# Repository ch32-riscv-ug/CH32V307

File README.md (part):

# CH32V307

<!-- This file is generated from ch32-riscv-ug/ch32-device-data (index/ + evidence/ + pipeline/build/build_readme.py). Edit there, not here. -->

[Choose a part](#product-comparison) &middot; [Documents](#documents) &middot; [Pin maps](#pin-maps--alternate-functions) &middot; [Pin viewer](https://ch32-riscv-ug.github.io/ch32-device-data/pins.html?chip=CH32V303) &middot; [Errata](#errata) &middot; [Examples](#evt-examples) &middot; [Address map](#address-map)

## Quick start

Programming and debug: **2-wire SDI** (WCH-Link, `Serial Debug Interface`).

### Debug / serial defaults

Where these land **without writing a remap register**. SWD is live at reset; the UART pads are not -- the pin must still be put into alternate-function mode. See `route` in evidence/README.ja.md.

| Series | SWDIO | SWCLK | UART TX | UART RX |
|---|---|---|---|---|
| CH32V303 | PA13 | PA14 | PA9 (USART1); PA2 (USART2) | PA10 (USART1); PA3 (USART2) |
| CH32V305 | PA13 | PA14 | PA9 (USART1); PA2 (USART2) | PA10 (USART1); PA3 (USART2) |
| CH32V307 | PA13 | PA14 | PA9 (USART1); PA2 (USART2) | PA10 (USART1); PA3 (USART2) |
| CH32V317 | PA13 | PA14 | PA9 (USART1); PA2 (USART2) | PA10 (USART1); PA3 (USART2) |

### Datasheets and reference manual

- CH32V20x_30xDS0.PDF (datasheet): [English](https://ch32-riscv-ug.github.io/CH32V307/datasheet_en/CH32V20x_30xDS0.PDF) · [中文](https://ch32-riscv-ug.github.io/CH32V307/datasheet_zh/CH32V20x_30xDS0.PDF)
- CH32FV2x_V3xRM.PDF (reference manual): [English](https://ch32-riscv-ug.github.io/CH32V307/datasheet_en/CH32FV2x_V3xRM.PDF) · [中文](https://ch32-riscv-ug.github.io/CH32V307/datasheet_zh/CH32FV2x_V3xRM.PDF)

## Series

Flash and SRAM list every value the series has; more than one means it varies by part number, and the per-part values are in the comparison table below.

| Series | Core | ISA | Flash | SRAM | Main clock | VDD | Packages | Products | Official |
|---|---|---|---|---|---|---|---|---|---|
| **CH32V303** | QingKe V4F | RV32IMACF | 128K/256K | 32K/64K | 144 MHz | 2.4-3.6V | LQFP100,LQFP48,LQFP64M | 5 | [en](https://www.wch-ic.com/products/CH32V303.html) / [zh](https://www.wch.cn/products/CH32V303.html) |
| **CH32V305** | QingKe V4F | RV32IMACF | 128K/256K | 32K/64K | 144 MHz | 2.4-3.6V | LQFP48,LQFP64M,QFN28,TSSOP20 | 4 | [en](https://www.wch-ic.com/products/CH32V305.html) / [zh](https://www.wch.cn/products/CH32V305.html) |
| **CH32V307** | QingKe V4F | RV32IMACF | 256K | 64K | 144 MHz | 2.4-3.6V | LQFP100,LQFP64M,QFN68 | 3 | [en](https://www.wch-ic.com/products/CH32V307.html) / [zh](https://www.wch.cn/products/CH32V307.html) |
| **CH32V317** | QingKe V4F | RV32IMACF | 256K | 64K | 144 MHz | 2.4-3.6V | LQFP100,QFN68 | 2 | [en](https://www.wch-ic.com/products/CH32V317.html) / [zh](https://www.wch.cn/products/CH32V317.html) |

## Product comparison

### CH32V303 product comparison

Only the 14 rows that differ between these 5 products; the other 11 are the same for all of them.

| | [CH32V303&#8203;CBT6](https://ch32-riscv-ug.github.io/ch32-device-data/pins.html?chip=CH32V303CBT6)&#8203;(LQFP48) | [CH32V303&#8203;RBT6](https://ch32-riscv-ug.github.io/ch32-device-data/pins.html?chip=CH32V303RBT6)&#8203;(LQFP64M) | [CH32V303&#8203;RCT6](https://ch32-riscv-ug.github.io/ch32-device-data/pins.html?chip=CH32V303RCT6)&#8203;(LQFP64M) | [CH32V303&#8203;RCT7](https://ch32-riscv-ug.github.io/ch32-device-data/pins.html?chip=CH32V303RCT7)&#8203;(LQFP64M) | [CH32V303&#8203;VCT6](https://ch32-riscv-ug.github.io/ch32-device-data/pins.html?chip=CH32V303VCT6)&#8203;(LQFP100) |
|---|---|---|---|---|---|
| **Flash (zero-wait)** | 128K | 128K | 256K | 256K | 256K |
| **SRAM** | 32K | 32K | 64K | 64K | 64K |
| **GPIO** | 37 | 51 | 51 | 51 | 80 |
| **Temperature** | -40..85C | -40..85C | -40..85C | -40..105C | -40..85C |
| Advanced-control (16-bit) | 1 | 1 | 4 | 4 | 4 |
| General-purpose (16-bit) | 3 | 3 | 4 | 4 | 4 |
| Basic (16-bit) | - | - | 2 | 2 | 2 |
| ADC/TKey Channel | 10 | 16 | 16 | 16 | 16 |
| USART/UART | 3 | 3 | 8 | 8 | 8 |
| SPI | 2 | 2 | 3 | 3 | 3 |
| RNG | - | - | 1 | 1 | 1 |
| I2S | - | - | 2 | 2 | 2 |
| SDIO | - | - | 1 | 1 | 1 |
| FSMC | - | - | - | - | 1 |

<details><summary>All 25 rows</summary>

| | [CH32V303&#8203;CBT6](https://ch32-riscv-ug.github.io/ch32-device-data/pins.html?chip=CH32V303CBT6)&#8203;(LQFP48) | [CH32V303&#8203;RBT6](https://ch32-riscv-ug.github.io/ch32-device-data/pins.html?chip=CH32V303RBT6)&#8203;(LQFP64M) | [CH32V303&#8203;RCT6](https://ch32-riscv-ug.github.io/ch32-device-data/pins.html?chip=CH32V303RCT6)&#8203;(LQFP64M) | [CH32V303&#8203;RCT7](https://ch32-riscv-ug.github.io/ch32-device-data/pins.html?chip=CH32V303RCT7)&#8203;(LQFP64M) | [CH32V303&#8203;VCT6](https://ch32-riscv-ug.github.io/ch32-device-data/pins.html?chip=CH32V303VCT6)&#8203;(LQFP100) |
|---|---|---|---|---|---|
| **Flash (zero-wait)** | 128K | 128K | 256K | 256K | 256K |
| **SRAM** | 32K | 32K | 64K | 64K | 64K |
| **GPIO** | 37 | 51 | 51 | 51 | 80 |
| **Temperature** | -40..85C | -40..85C | -40..85C | -40..105C | -40..85C |
| Code FLASH, total (bytes) | 480K | 480K | 480K | 480K | 480K |
| Advanced-control (16-bit) | 1 | 1 | 4 | 4 | 4 |
| General-purpose (16-bit) | 3 | 3 | 4 | 4 | 4 |
| Timer Watchdog | 2 (WWDG + IWDG) | 2 (WWDG + IWDG) | 2 (WWDG + IWDG) | 2 (WWDG + IWDG) | 2 (WWDG + IWDG) |
| Basic (16-bit) | - | - | 2 | 2 | 2 |
| SysTick (64-bit) | Supported | Supported | Supported | Supported | Supported |
| RTC | Supported | Supported | Supported | Supported | Supported |
| ADC/TKey Unit | 2 | 2 | 2 | 2 | 2 |
| ADC/TKey Channel | 10 | 16 | 16 | 16 | 16 |
| DAC (Unit) | 2 | 2 | 2 | 2 | 2 |
| OPA/CMP | 4 | 4 | 4 | 4 | 4 |
| USART/UART | 3 | 3 | 8 | 8 | 8 |
| SPI | 2 | 2 | 3 | 3 | 3 |
| RNG | - | - | 1 | 1 | 1 |
| I2C | 2 | 2 | 2 | 2 | 2 |
| CAN | 1 | 1 | 1 | 1 | 1 |
| USBHD | 1 | 1 | 1 | 1 | 1 |
| I2S | - | - | 2 | 2 | 2 |
| CPU main frequency | Max: 144MHz | Max: 144MHz | Max: 144MHz | Max: 144MHz | Max: 144MHz |
| SDIO | - | - | 1 | 1 | 1 |
| FSMC | - | - | - | - | 1 |

</details>

### CH32V305 product comparison

Only the 13 rows that differ between these 4 products; the other 12 are the same for all of them.

| | [CH32V305&#8203;CCT6](https://ch32-riscv-ug.github.io/ch32-device-data/pins.html?chip=CH32V305CCT6)&#8203;(LQFP48) | [CH32V305&#8203;FBP6](https://ch32-riscv-ug.github.io/ch32-device-data/pins.html?chip=CH32V305FBP6)&#8203;(TSSOP20) | [CH32V305&#8203;GBU6](https://ch32-riscv-ug.github.io/ch32-device-data/pins.html?chip=CH32V305GBU6)&#8203;(QFN28) | [CH32V305&#8203;RBT6](https://ch32-riscv-ug.github.io/ch32-device-data/pins.html?chip=CH32V305RBT6)&#8203;(LQFP64M) |
|---|---|---|---|---|
| **Flash (zero-wait)** | 256K | 128K | 128K | 128K |
| **SRAM** | 64K | 32K | 32K | 32K |
| **GPIO** | 41 | 17 | 24 | 51 |
| Code FLASH, total (bytes) | 480K | 224K | 224K | 480K |
| ADC/TKey Channel | 16 | 1 | 6 | 16 |
| DAC (Unit) | 2 | DAC2 | 2 | 2 |
| OPA/CMP | 4 | - | OPA3 | 4 |
| USART/UART | 5 | USART1 USART3 | USART1 USART3 UART4 UART5 UART7 | 5 |
| SPI | 3 | SPI2 | 3 | 3 |
| I2S | 2 | I2S2 | 2 | 2 |
| CAN | 2 | CAN2 | CAN2 | 2 |
| USBHD | 1 | - | - | 1 |
| SDIO | - | - | 1 | 1 |

<details><summary>All 25 rows</summary>

| | [CH32V305&#8203;CCT6](https://ch32-riscv-ug.github.io/ch32-device-data/pins.html?chip=CH32V305CCT6)&#8203;(LQFP48) | [CH32V305&#8203;FBP6](https://ch32-riscv-ug.github.io/ch32-device-data/pins.html?chip=CH32V305FBP6)&#8203;(TSSOP20) | [CH32V305&#8203;GBU6](https://ch32-riscv-ug.github.io/ch32-device-data/pins.html?chip=CH32V305GBU6)&#8203;(QFN28) | [CH32V305&#8203;RBT6](https://ch32-riscv-ug.github.io/ch32-device-data/pins.html?chip=CH32V305RBT6)&#8203;(LQFP64M) |
|---|---|---|---|---|
| **Flash (zero-wait)** | 256K | 128K | 128K | 128K |
| **SRAM** | 64K | 32K | 32K | 32K |
| **GPIO** | 41 | 17 | 24 | 51 |
| **Temperature** | -40..85C | -40..85C | -40..85C | -40..85C |
| Code FLASH, total (bytes) | 480K | 224K | 224K | 480K |
| Advanced-control (16-bit) | 4 | 4 | 4 | 4 |
| General-purpose (16-bit) | 4 | 4 | 4 | 4 |
| Basic (16-bit) | 2 | 2 | 2 | 2 |
| Timer Watchdog | 2 (WWDG + IWDG) | 2 (WWDG + IWDG) | 2 (WWDG + IWDG) | 2 (WWDG + IWDG) |
| SysTick (64-bit) | Supported | Supported | Supported | Supported |
| RTC | Supported | Supported | Supported | Supported |
| ADC/TKey Unit | 2 | 2 | 2 | 2 |
| ADC/TKey Channel | 16 | 1 | 6 | 16 |
| DAC (Unit) | 2 | DAC2 | 2 | 2 |
| OPA/CMP | 4 | - | OPA3 | 4 |
| RNG | 1 | 1 | 1 | 1 |
| USART/UART | 5 | USART1 USART3 | USART1 USART3 UART4 UART5 UART7 | 5 |
| SPI | 3 | SPI2 | 3 | 3 |
| I2S | 2 | I2S2 | 2 | 2 |
| I2C | 2 | 2 | 2 | 2 |
| CAN | 2 | CAN2 | CAN2 | 2 |
| USBHS (include PHY) | 1 | 1 | 1 | 1 |
| USBHD | 1 | - | - | 1 |
| CPU main frequency | Max: 144MHz | Max: 144MHz | Max: 144MHz | Max: 144MHz |
| SDIO | - | - | 1 | 1 |

</details>

### CH32V307 product comparison

Only the 3 rows that differ between these 3 products; the other 25 are the same for all of them.

| | [CH32V307&#8203;RCT6](https://ch32-riscv-ug.github.io/ch32-device-data/pins.html?chip=CH32V307RCT6)&#8203;(LQFP64M) | [CH32V307&#8203;VCT6](https://ch32-riscv-ug.github.io/ch32-device-data/pins.html?chip=CH32V307VCT6)&#8203;(LQFP100) | [CH32V307&#8203;WCU6](https://ch32-riscv-ug.github.io/ch32-device-data/pins.html?chip=CH32V307WCU6)&#8203;(QFN68) |
|---|---|---|---|
| **GPIO** | 51 | 80 | 54 |
| DVP | - | 1 | - |
| FSMC | - | 1 | - |

<details><summary>All 28 rows</summary>

| | [CH32V307&#8203;RCT6](https://ch32-riscv-ug.github.io/ch32-device-data/pins.html?chip=CH32V307RCT6)&#8203;(LQFP64M) | [CH32V307&#8203;VCT6](https://ch32-riscv-ug.github.io/ch32-device-data/pins.html?chip=CH32V307VCT6)&#8203;(LQFP100) | [CH32V307&#8203;WCU6](https://ch32-riscv-ug.github.io/ch32-device-data/pins.html?chip=CH32V307WCU6)&#8203;(QFN68) |
|---|---|---|---|
| **Flash (zero-wait)** | 256K | 256K | 256K |
| **SRAM** | 64K | 64K | 64K |
| **GPIO** | 51 | 80 | 54 |
| **Temperature** | -40..85C | -40..85C | -40..85C |
| Code FLASH, total (bytes) | 480K | 480K | 480K |
| Advanced-control (16-bit) | 4 | 4 | 4 |
| General-purpose (16-bit) | 4 | 4 | 4 |
| Basic (16-bit) | 2 | 2 | 2 |
| Timer Watchdog | 2 (WWDG + IWDG) | 2 (WWDG + IWDG) | 2 (WWDG + IWDG) |
| SysTick (64-bit) | Supported | Supported | Supported |
| RTC | Supported | Supported | Supported |
| ADC/TKey Unit | 2 | 2 | 2 |
| ADC/TKey Channel | 16 | 16 | 16 |
| DAC (Unit) | 2 | 2 | 2 |
| OPA/CMP | 4 | 4 | 4 |
| RNG | 1 | 1 | 1 |
| USART/UART | 8 | 8 | 8 |
| SPI | 3 | 3 | 3 |
| I2S | 2 | 2 | 2 |
| I2C | 2 | 2 | 2 |
| CAN | 2 | 2 | 2 |
| SDIO | 1 | 1 | 1 |
| USBHD | 1 | 1 | 1 |
| USBHS (include PHY) | 1 | 1 | 1 |
| Ethernet | 1G MAC+10M PHY | 1G MAC+10M PHY | 1G MAC+10M PHY |
| CPU main frequency | Max: 144MHz | Max: 144MHz | Max: 144MHz |
| DVP | - | 1 | - |
| FSMC | - | 1 | - |

</details>

### CH32V317 product comparison

Only the 2 rows that differ between these 2 products; the other 25 are the same for all of them.

| | [CH32V317&#8203;VCT6](https://ch32-riscv-ug.github.io/ch32-device-data/pins.html?chip=CH32V317VCT6)&#8203;(LQFP100) | [CH32V317&#8203;WCU6](https://ch32-riscv-ug.github.io/ch32-device-data/pins.html?chip=CH32V317WCU6)&#8203;(QFN68) |
|---|---|---|
| **GPIO** | 70 | 48 |
| DVP | 1 | - |

<details><summary>All 27 rows</summary>

| | [CH32V317&#8203;VCT6](https://ch32-riscv-ug.github.io/ch32-device-data/pins.html?chip=CH32V317VCT6)&#8203;(LQFP100) | [CH32V317&#8203;WCU6](https://ch32-riscv-ug.github.io/ch32-device-data/pins.html?chip=CH32V317WCU6)&#8203;(QFN68) |
|---|---|---|
| **Flash (zero-wait)** | 256K | 256K |
| **SRAM** | 64K | 64K |
| **GPIO** | 70 | 48 |
| **Temperature** | -40..85C | -40..85C |
| Code FLASH, total (bytes) | 480K | 480K |
| Advanced-control (16-bit)(2) | 4 | 4 |
| General-purpose (16-bit)(2) | 4 | 4 |
| Basic (16-bit) | 2 | 2 |
| Timer Watchdog | 2 (WWDG + IWDG) | 2 (WWDG + IWDG) |
| SysTick (64-bit) | Supported | Supported |
| RTC | Supported | Supported |
| ADC/TKey Unit | 2 | 2 |
| ADC/TKey Channel | 16 | 16 |
| DAC (Unit) | 2 | 2 |
| OPA | 4 | 4 |
| RNG | 1 | 1 |
| USART/UART | 8 | 8 |
| SPI | 3 | 3 |
| I2S | 2 | 2 |
| I2C | 2 | 2 |
| CAN | 2 | 2 |
| SDIO | 1 | 1 |
| USBHD | 1 | 1 |
| USBHS (include PHY) | 1 | 1 |
| Ethernet | MAC+10M/100M PHY | MAC+10M/100M PHY |
| DVP | 1 | - |
| CPU main frequency | Max: 144MHz | Max: 144MHz |

</details>

## Block diagrams

### CH32V303

System block diagram from the [WCH product page](https://www.wch-ic.com/products/CH32V303.html).

<details><summary>Internal block diagram (datasheet)</summary>

</details>

### CH32V305

<details><summary>Internal block diagram (datasheet)</summary>

</details>

### CH32V307

System block diagram from the [WCH product page](https://www.wch-ic.com/products/CH32V307.html).

<details><summary>Internal block diagram (datasheet)</summary>

</details>

### CH32V317

System block diagram from the [WCH product page](https://www.wch-ic.com/products/CH32V317.html).

<details><summary>Internal block diagram (datasheet)</summary>

</details>

## Documents

| Document | Kind | English | 中文 |
|---|---|---|---|
| CH32V20x_30xDS0.PDF | datasheet | [page](https://www.wch-ic.com/downloads/CH32V20x_30xDS0_PDF.html) [mirror](https://ch32-riscv-ug.github.io/CH32V307/datasheet_en/CH32V20x_30xDS0.PDF) v3.5 | [page](https://www.wch.cn/downloads/CH32V20x_30xDS0_PDF.html) [mirror](https://ch32-riscv-ug.github.io/CH32V307/datasheet_zh/CH32V20x_30xDS0.PDF) v3.5 |
| CH32FV2x_V3xRM.PDF | reference-manual | [page](https://www.wch-ic.com/downloads/CH32FV2x_V3xRM_PDF.html) [mirror](https://ch32-riscv-ug.github.io/CH32V307/datasheet_en/CH32FV2x_V3xRM.PDF) v2.5 | [page](https://www.wch.cn/downloads/CH32FV2x_V3xRM_PDF.html) [mirror](https://ch32-riscv-ug.github.io/CH32V307/datasheet_zh/CH32FV2x_V3xRM.PDF) v2.5 |
| CH32V307EVT.ZIP | evt | - | [page](https://www.wch.cn/downloads/CH32V307EVT_ZIP.html) [mirror](https://github.com/ch32-riscv-ug/CH32V307/tree/main/EVT) v3.2 |

### Evaluation boards

- board-manual:en: [CH32V30x Evaluation Board Reference-EN.pdf](https://ch32-riscv-ug.github.io/CH32V307/EVT/PUB/CH32V30x%20Evaluation%20Board%20Reference-EN.pdf)
- board-manual:zh: [CH32V30x评估板说明书.pdf](https://ch32-riscv-ug.github.io/CH32V307/EVT/PUB/CH32V30x%E8%AF%84%E4%BC%B0%E6%9D%BF%E8%AF%B4%E6%98%8E%E4%B9%A6.pdf)
- schematic-pdf: [CH32V30xSCH.pdf](https://ch32-riscv-ug.github.io/CH32V307/EVT/PUB/CH32V30xSCH.pdf)

13 board schematics under `EVT/PUB/SCHPCB/`: `CH32V303CBT6-R0`, `CH32V303RBT6-R1`, `CH32V303RCT6-R1`, `CH32V303VCT6-R0`, `CH32V303VCT6-R1`, `CH32V305FBP6-R0`, `CH32V305GBU6-R0`, `CH32V305RBT6-R1`, `CH32V307RCT6-R1`, `CH32V307VCT6-R0`, `CH32V307VCT6-R1`, `CH32V307WCU6-R0`, `CH32V317WCU6-R0`

## Packages & pinout drawings

Pinout drawings are in the datasheet (chapter *Pinouts*); each link opens at the page that carries the drawing:

| Package | Products | Datasheet | Outline |
|---|---|---|---|
| LQFP48 | CH32V303CBT6 | [en](https://ch32-riscv-ug.github.io/CH32V307/datasheet_en/CH32V20x_30xDS0.PDF#page=27) / [zh](https://ch32-riscv-ug.github.io/CH32V307/datasheet_zh/CH32V20x_30xDS0.PDF#page=22) | [drawing](https://raw.githubusercontent.com/ch32-riscv-ug/WCH-common/main/image/package_LQFP48.png) |
| LQFP64M | CH32V303RBT6, CH32V303RCT6, CH32V303RCT7, CH32V305RBT6, CH32V307RCT6 | [en](https://ch32-riscv-ug.github.io/CH32V307/datasheet_en/CH32V20x_30xDS0.PDF#page=27) / [zh](https://ch32-riscv-ug.github.io/CH32V307/datasheet_zh/CH32V20x_30xDS0.PDF#page=22) | [drawing](https://raw.githubusercontent.com/ch32-riscv-ug/WCH-common/main/image/package_LQFP64M.png) |
| LQFP100 | CH32V303VCT6, CH32V307VCT6 | [en](https://ch32-riscv-ug.github.io/CH32V307/datasheet_en/CH32V20x_30xDS0.PDF#page=27) / [zh](https://ch32-riscv-ug.github.io/CH32V307/datasheet_zh/CH32V20x_30xDS0.PDF#page=22) | [drawing](https://raw.githubusercontent.com/ch32-riscv-ug/WCH-common/main/image/package_LQFP100.png) |
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
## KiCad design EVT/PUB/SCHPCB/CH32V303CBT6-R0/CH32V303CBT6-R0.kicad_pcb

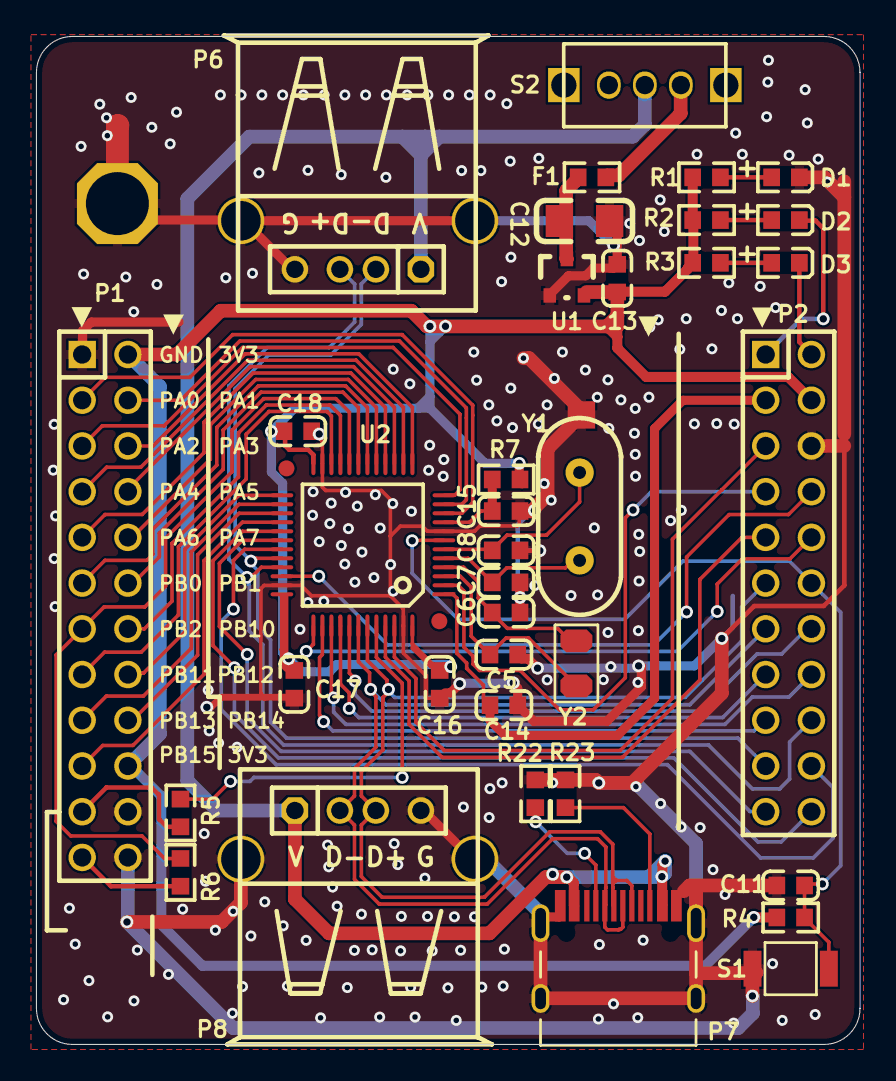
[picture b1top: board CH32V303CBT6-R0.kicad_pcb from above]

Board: 2 copper layers, 45.8 x 56.0 mm, 36 parts (0 on the bottom side), 55 nets.

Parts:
C5, C6: 12pF; 0603_C
C7, C8: 22pF; 0603_C
C11, C14, C15, C16, C17, C18: 0.1uF; 0603_C
C12: 10uF; 3216_C
C13: 2.2uF; 0603_C
D1: POWER red; 0603+
D2: LED1; 0603+
D3: LED2; 0603+
F1: 500mA; 0603
P1: HEADER 12x2; IDC24-2.54MM
P2: HEADER 11x2; IDC22-2.54MM
P6, P8: USB_A; USBAF
P7: TYPE-C; TYPE-C-Receptacle-2.0
R1, R2, R3: 1K; 0603
R4, R5, R6: 10K; 0603
R7: 0Ω; 0603
R22, R23: NC(5.1K); 0603
S1: KEY; 贴片按键
S2: SW; KEY2
U1: 6219P33M; SOT-23
U2: CH32V203CxT; LQFP48
Y1: 8M; XT_AT49
Y2: 32.768k; FC-135

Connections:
+5V: P6.1, P7.A4, P7.B4, P8.1, S2.1
BOOT0: R5.1, U2.44
BOOT1: P1.13, R6.1, U2.20
GND: C5.2, C6.2, C7.1, C8.1, C11.1, C12.2, C13.2, C14.2, C15.2, C16.1, C17.1, C18.1, D1.2, P1.1, P1.22, P1.24, P2.6, P6.0, P6.4, P7.0, P7.A1, P7.B1, P8.0, P8.4, R22.2, R23.2, S1.2, U1.1, U2.8, U2.23, U2.35, U2.47, Y1.0
LED1: D2.2, P2.1
LED2: D3.2, P2.2
NRST: C11.2, P2.12, R4.1, S1.1, U2.7
NetD1_1: D1.1, R1.1
NetD2_1: D2.1, R2.2
NetD3_1: D3.1, R3.2
NetF1_1: F1.1, S2.3
NetP1_21: P1.21, R5.2
NetP1_23: P1.23, R6.2
NetP7_A5: P7.A5, R22.1
NetP7_B5: P7.B5, R23.1
PA0: P1.3, U2.10
PA1: P1.4, U2.11
PA2: P1.5, U2.12
PA3: P1.6, U2.13
PA4: P1.7, U2.14
PA5: P1.8, U2.15
PA6: P1.9, U2.16
PA7: P1.10, U2.17
PA8: P2.22, U2.29
PA9: P2.21, U2.30
PA10: P2.20, U2.31
PA11: P2.19, P6.2, U2.32
PA12: P2.18, P6.3, U2.33
PA13: P2.8, U2.34
PA14: P2.10, U2.37
PA15: P2.17, U2.38
PB0: P1.11, U2.18
PB1: P1.12, U2.19
PB3: P2.16, U2.39
PB4: P2.15, U2.40
PB5: P2.14, U2.41
PB6: P2.13, P7.A7, P7.B7, P8.2, U2.42
PB7: P2.11, P7.A6, P7.B6, P8.3, U2.43
PB8: P2.9, U2.45
PB9: P2.5, U2.46
PB10: P1.14, U2.21
PB11: P1.15, U2.22
PB12: P1.16, U2.25
PB13: P1.17, U2.26
PB14: P1.18, U2.27
PB15: P1.19, U2.28
PC13: P2.7, U2.2
PC14: C5.1, U2.3, Y2.1
PC15: C6.1, U2.4, Y2.2
PD0: C7.2, U2.5, Y1.2
PD1: C8.2, U2.6, Y1.1
V5V: C12.1, F1.2, U1.3
VBAT: C14.1, P2.3, U2.1
VCC: C13.1, C16.2, C17.2, C18.2, P1.2, P1.20, P2.4, R1.2, R2.1, R3.1, R4.2, R7.1, U1.2, U2.24, U2.36, U2.48
VDDA: C15.1, R7.2, U2.9

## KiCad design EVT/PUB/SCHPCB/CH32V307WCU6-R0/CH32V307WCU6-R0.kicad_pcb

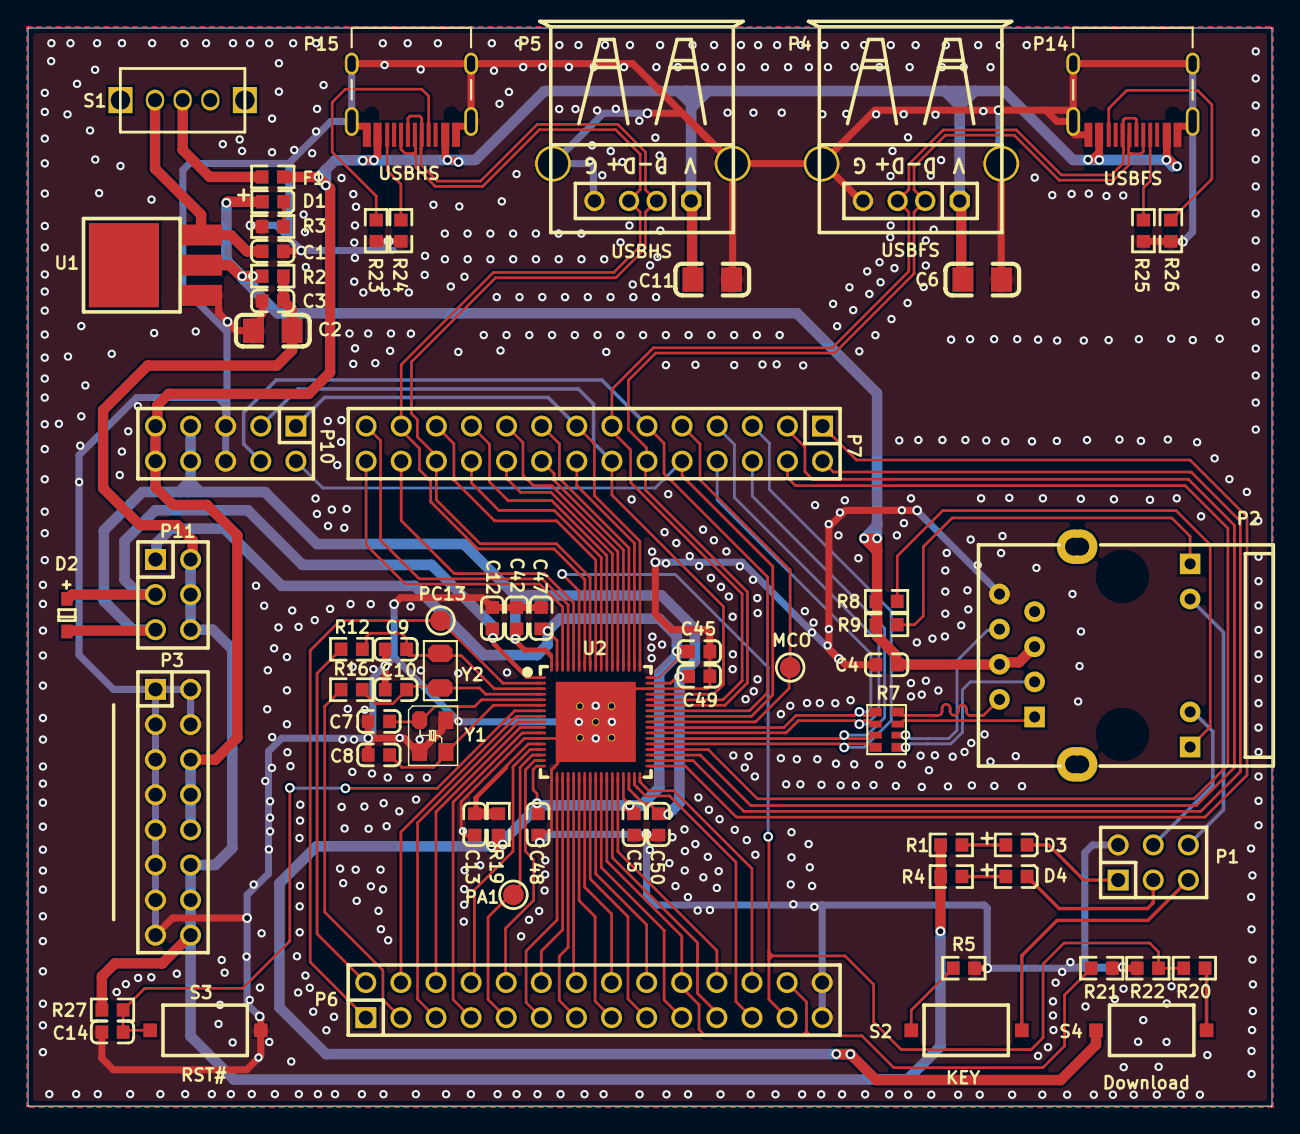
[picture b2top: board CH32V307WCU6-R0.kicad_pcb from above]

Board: 2 copper layers, 90.0 x 78.0 mm, 66 parts (0 on the bottom side), 88 nets.

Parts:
C1, C3, C4, C5, C12, C13, C14, C42, C45, C47, C48, C49, C50: 0.1uF; 0603_C
C2, C6, C11: 10uF; 3216_C
C7, C8: 22pF; 0603_C
C9, C10: 12pF; 0603_C
D1, D4: RED; 0603+
D2: B0520WS; SOD-323
D3: BLUE; 0603+
F1: 500mA; 0603
MCO: Testpoint; TESTPOINT1
P1: IO; IDC6-2.54mm
P2: HR911105A
P3: Ppin; IDC16-2.54mm
P4: USBFS; USBAF
P5: USBHS; USBAF
P6, P7: HEADER 14x2; IDC28-2.54MM
P10: LINK; IDC10-2.54mm
P11: Psel; IDC6-2.54mm
P14: USBFS; TYPE-C-Receptacle-2.0
P15: USBHS; TYPE-C-Receptacle-2.0
PA1: Testpoint; TESTPOINT1
PC13: Testpoint; TESTPOINT1
R1, R3, R4, R8, R9, R20: 1K; 0603
R2, R19: 0R; 0603
R5, R21, R22, R27: 10K; 0603
R7: 0Ω; 8P4R-0603
R12, R16: NC(0R); 0603
R23, R24, R25, R26: 5.1K; 0603
S1: SW SPDT; KEY2
S2: KEY; SMD_6.1x3.65x2.5mm-KEY
S3: RST#; SMD_6.1x3.65x2.5mm-KEY
S4: Download; SMD_6.1x3.65x2.5mm-KEY
U1: 1117-3.3V; SOT-223
U2: CH32V307W; QFN68_8x8
Y1: 8MHz; XT3225
Y2: 32768Hz; FC-135

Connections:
3V3: C2.1, C3.1, P3.12, P3.14, P3.16, P11.2, P11.4, P11.6, R1.1, R2.1, R4.1, R27.2
3V3S: C4.2, D1.1, P2.4, P2.5, R2.2, R8.1, R9.1, U1.2
5V: C6.1, C11.1, F1.1, P3.6, P3.8, P3.10, P4.1, P5.1, P10.9, P10.10, P14.A4, P14.B4, P15.A4, P15.B4
BOOT0: P6.25, R20.1, R22.1, U2.63
BOOT1: P6.20, P6.26, R21.1, U2.28
ELED1: P1.4, P2.10
ELED2: P1.6, P2.11
ERXN: P7.6, R7.3, U2.40
ERXN1: P2.6, R7.6
ERXP: P7.5, R7.4, U2.39
ERXP1: P2.3, R7.5
ETXN: P7.8, R7.1, U2.42
ETXN1: P2.2, R7.8
ETXP: P7.7, R7.2, U2.41
ETXP1: P2.1, R7.7
GND: C1.2, C2.2, C3.2, C4.1, C5.1, C6.2, C7.1, C8.1, C9.1, C10.1, C11.2, C12.1, C13.2, C14.1, C42.1, C45.2, C47.2, C48.2, C49.1, C50.2, P1.2, P2.8, P3.1, P3.2, P3.3, P3.4, P3.5, P3.7, P3.9, P3.11, P3.13, P3.15, P4.0, P4.4, P5.0, P5.4, P6.27, P6.28, P10.5, P10.6, P14.0, P14.A1, P14.B1, P15.0, P15.A1, P15.B1, R3.2, R5.1, R21.2, R22.2, R23.2, R24.2, R25.2, R26.2, S3.1, U1.1, U2.0, U2.12, U2.18, U2.49, Y1.2, Y1.4
KEY: P1.5, S2.1
LED1: D3.2, P1.1
LED2: D4.2, P1.3
MCO: MCO.1, P7.9, U2.43
NRST: C14.2, R27.1, S3.2, U2.7
NetC1_1: C1.1, S1.2, U1.3
NetD1_2: D1.2, R3.1
NetD3_1: D3.1, R1.2
NetD4_1: D4.1, R4.2
NetF1_2: F1.2, S1.1
NetP2_9: P2.9, R8.2
NetP2_12: P2.12, R9.2
NetP14_A5: P14.A5, R25.1
NetP14_B5: P14.B5, R26.1
NetP15_A5: P15.A5, R23.1
NetP15_B5: P15.B5, R24.1
NetR5_2: R5.2, S2.2
NetR20_2: R20.2, S4.2
PA0: P6.8, U2.14
PA1: P6.9, PA1.1, U2.15
PA2: P6.10, U2.16
PA3: P6.11, U2.19
PA4: P6.12, U2.20
PA5: P6.13, U2.21
PA6: P6.14, U2.22
PA7: P6.15, U2.23
PA9: P7.10, P10.2, U2.44
PA10: P7.11, P10.4, U2.45
PA11: P4.2, P7.12, P14.A7, P14.B7, U2.46
PA12: P4.3, P7.13, P14.A6, P14.B6, U2.47
PA13: P7.14, P10.3, U2.48
PA14: P7.15, P10.1, U2.52
PA15: P7.16, U2.53
PB0: P6.18, U2.26
PB1: P6.19, U2.27
PB3: P7.21, U2.58
PB4: P7.22, U2.59
PB5: P7.23, U2.60
PB6: P5.2, P7.24, P15.A7, P15.B7, U2.61
PB7: P5.3, P7.25, P15.A6, P15.B6, U2.62
PB8: P7.26, U2.64
PB9: P7.27, U2.65
PB10: P6.21, U2.29
PB11: P6.22, U2.30
PB12: P7.1, U2.35
PB13: P7.2, U2.36
PB14: P7.3, U2.37
PB15: P7.4, U2.38
PC0: P6.4, U2.8
PC1: P6.5, U2.9
PC2: P6.6, U2.10
PC3: P6.7, U2.11
PC4: P6.16, U2.24
PC5: P6.17, U2.25
PC10: P7.17, U2.54
PC11: P7.18, U2.55
PC12: P7.19, U2.56
PC13: P6.1, PC13.1, U2.2
PC14: P6.2, R12.1
PC15: P6.3, R16.1
PD2: P7.20, U2.57
PD8: P6.23, U2.33
PD9: P6.24, U2.34
PE0: P7.28, U2.66
VBAT: C12.2, D2.1, P11.3, U2.1
VDD: C42.2, C49.2, C50.1, D2.2, P10.7, P10.8, P11.5, U2.32, U2.50, U2.68
VDDA: C13.1, R19.2, U2.13
VIO: C5.2, C45.1, C47.1, C48.1, P11.1, R19.1, S4.1, U2.17, U2.31, U2.51, U2.67
X32KI: C9.2, R12.2, U2.3, Y2.1
X32KO: C10.2, R16.2, U2.4, Y2.2
XI: C7.2, U2.5, Y1.1
XO: C8.2, U2.6, Y1.3

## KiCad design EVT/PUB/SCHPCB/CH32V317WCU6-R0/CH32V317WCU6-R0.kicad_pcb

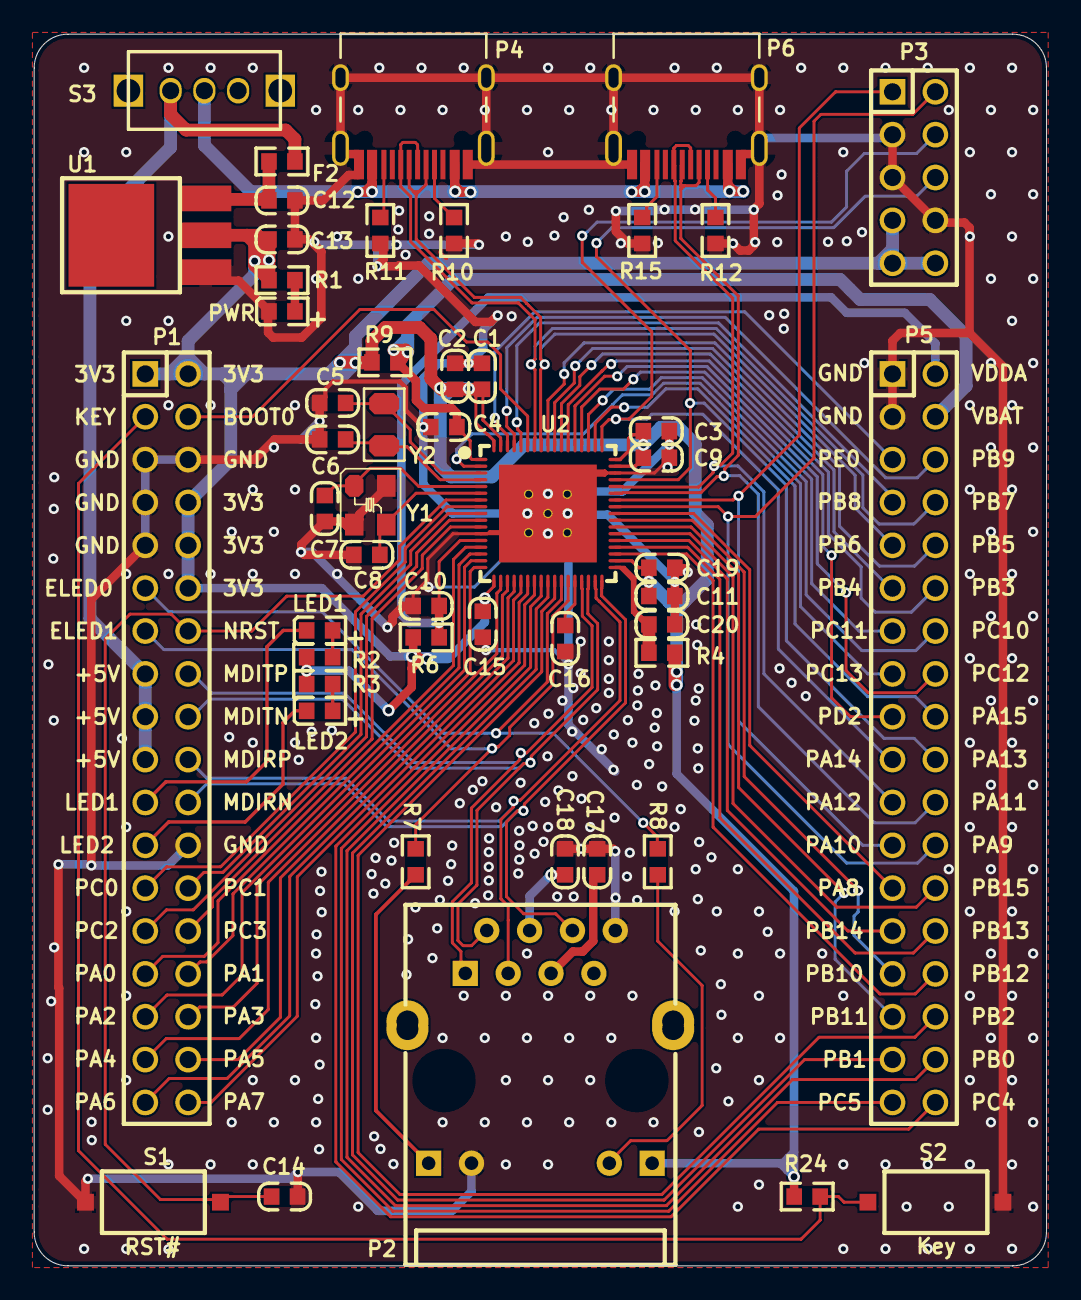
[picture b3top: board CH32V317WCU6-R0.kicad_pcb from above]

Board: 2 copper layers, 60.0 x 73.0 mm, 50 parts (0 on the bottom side), 79 nets.

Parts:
C1, C2, C3, C4, C9, C10, C11, C14, C15, C17, C18: 0.1uF; 0603_C
C5, C6: 12pF; 0603_C
C7, C8: 20pF; 0603_C
C12, C13, C19: 10uF; 0603_C
C16, C20: 1uF; 0603_C
F2: 500mA; 0603
LED1: LED1 blue; 0603+
LED2: LED2 blue; 0603+
P1, P5: Header 18X2; IDC36-2.54mm
P2: HR911105A
P3: Header 5X2; IDC10-2.54mm
P4: USBHS; TYPE-C-Receptacle-2.0
P6: USBFS; TYPE-C-Receptacle-2.0
PWR: POWER red; 0603+
R1, R2, R3: 1K; 0603
R4: 0Ω; 0603
R6, R9: 0R; 0603
R7, R8: 470Ω; 0603
R10, R11, R12, R15: NC(5.1K); 0603
R24: 10K; 0603
S1: RST#; SMD_6.1x3.65x2.5mm-KEY
S2: Key; SMD_6.1x3.65x2.5mm-KEY
S3: SW; SW1
U1: 1117-3.3V; SOT-223
U2: CH32V317W; QFN68_8X8
Y1: 8M; XT3225
Y2: 32.768k; FC-135

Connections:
3V3: C1.2, C2.2, C3.2, C9.2, C11.2, C13.1, C15.2, C19.2, P1.1, P1.2, P1.8, P1.10, P1.12, P2.12, P3.7, P3.9, P3.10, R1.2, R2.1, R3.1, R4.2, R6.1, R9.1, R24.2, U1.2, U2.18, U2.36, U2.50, U2.51, U2.67, U2.68
5V: P4.A4, P4.B4, P6.A4, P6.B4, S3.1
+5V: F2.1, P1.15, P1.17, P1.19, S3.3
BOOT0: P1.4, U2.63
ELED0: P1.11, R8.1, U2.28
ELED1: P1.13, R7.1, U2.29
GND: C1.1, C2.1, C3.1, C4.1, C5.2, C6.2, C7.1, C8.1, C9.1, C10.2, C11.1, C12.2, C13.2, C14.1, C15.1, C16.1, C17.1, C18.1, C19.1, C20.1, P1.5, P1.6, P1.7, P1.9, P1.24, P2.8, P2.10, P3.3, P3.5, P3.8, P4.0, P4.A1, P4.B1, P5.1, P5.3, P6.0, P6.A1, P6.B1, PWR.2, R10.1, R11.1, R12.1, R15.1, S1.1, S2.2, U1.1, U2.0, U2.12, U2.49, Y1.2, Y1.4
KEY: P1.3, R24.1, S2.1
LED1: LED1.2, P1.21
LED2: LED2.2, P1.23
MDIRN: P1.22, P2.6, U2.34
MDIRP: P1.20, P2.3, U2.33
MDITN: P1.18, P2.2, U2.32
MDITP: P1.16, P2.1, U2.31
NRST: C14.2, P1.14, S1.2, U2.7
NetC12_1: C12.1, F2.2, U1.3
NetC17_2: C17.2, P2.5
NetC18_2: C18.2, P2.4
NetLED1_1: LED1.1, R2.2
NetLED2_1: LED2.1, R3.2
NetP2_9: P2.9, R7.2
NetP2_11: P2.11, R8.2
NetP4_A5: P4.A5, R10.2
NetP4_B5: P4.B5, R11.2
NetP6_A5: P6.A5, R12.2
NetP6_B5: P6.B5, R15.2
NetPWR_1: PWR.1, R1.1
PA0: P1.29, U2.14
PA1: P1.30, U2.15
PA2: P1.31, U2.16
PA3: P1.32, U2.17
PA4: P1.33, U2.19
PA5: P1.34, U2.20
PA6: P1.35, U2.21
PA7: P1.36, U2.22
PA8: P5.25, U2.43
PA9: P3.2, P5.24, U2.44
PA10: P3.1, P5.23, U2.45
PA11: P5.22, P6.A7, P6.B7, U2.46
PA12: P5.21, P6.A6, P6.B6, U2.47
PA13: P3.6, P5.20, U2.48
PA14: P3.4, P5.19, U2.52
PA15: P5.18, U2.53
PB0: P5.34, U2.25
PB1: P5.33, U2.26
PB2: P5.32, U2.27
PB3: P5.12, U2.58
PB4: P5.11, U2.59
PB5: P5.10, U2.60
PB6: P4.A7, P4.B7, P5.9, U2.61
PB7: P4.A6, P4.B6, P5.8, U2.62
PB8: P5.7, U2.64
PB9: P5.6, U2.65
PB10: P5.29, U2.42
PB11: P5.31, U2.41
PB12: P5.30, U2.37
PB13: P5.28, U2.38
PB14: P5.27, U2.39
PB15: P5.26, U2.40
PC0: P1.25, U2.8
PC1: P1.26, U2.9
PC2: P1.27, U2.10
PC3: P1.28, U2.11
PC4: P5.36, U2.23
PC5: P5.35, U2.24
PC10: P5.14, U2.54
PC11: P5.13, U2.55
PC12: P5.16, U2.56
PC13: P5.15, U2.2
PD2: P5.17, U2.57
PE0: P5.5, U2.66
VBAT: C4.2, P5.4, R9.2, U2.1
VDDA: C10.1, P5.2, R6.2, U2.13
VDDK: C16.2, U2.30
VDD_ETH: C20.2, R4.1, U2.35
X32KI: C5.1, U2.3, Y2.1
X32KO: C6.1, U2.4, Y2.2
XI: C7.2, U2.5, Y1.1
XO: C8.2, U2.6, Y1.3

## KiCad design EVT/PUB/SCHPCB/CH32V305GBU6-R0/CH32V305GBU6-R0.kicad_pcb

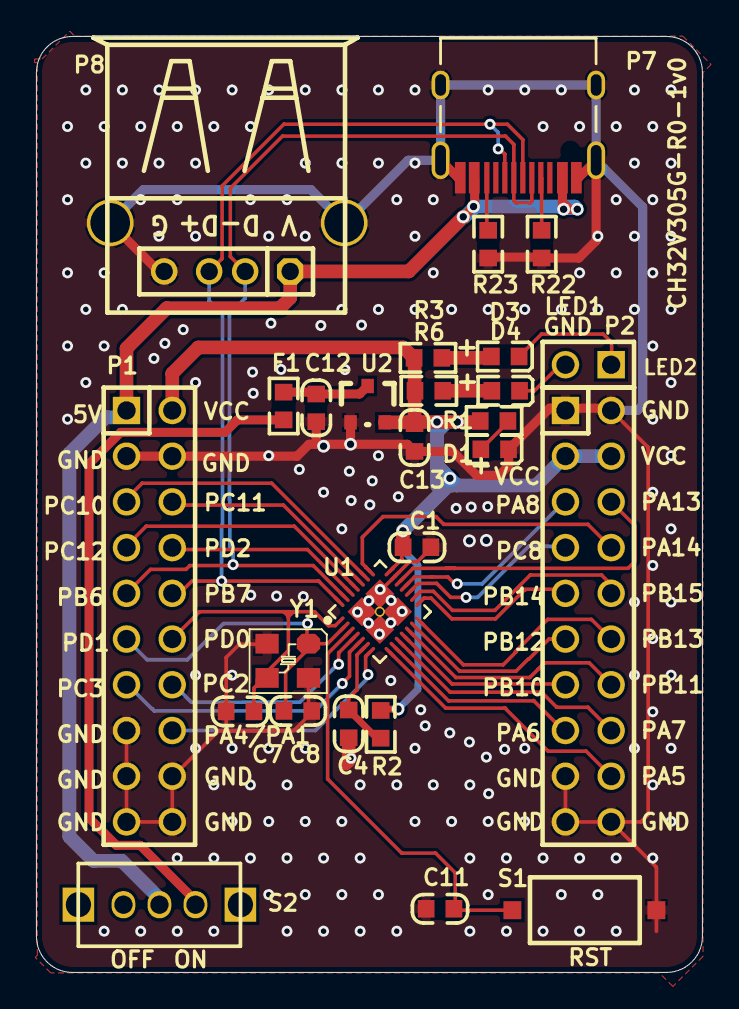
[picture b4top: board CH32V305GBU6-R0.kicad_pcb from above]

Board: 2 copper layers, 37.0 x 52.0 mm, 27 parts (0 on the bottom side), 38 nets.

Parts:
C1, C4, C11: 0.1uF; 0603_C
C7, C8: 22pF; 0603_C
C12: 10uF; 0603_C
C13: 2.2uF; 0603_C
D1: POWER red; 0603+
D3: LED2; 0603+
D4: LED1; 0603+
F1: 500mA; 0603
P1, P2: Header 10X2; IDC20-2.54mm
P4: HEADER 2; SIP2-2.54mm
P7: TYPE-C; TYPE-C-Receptacle-2.0
P8: USB_A; USBAF
R1, R2, R3, R6: 1K; 0603
R22, R23: 5.1K; 0603
S1: RST; SMD_6.1x3.65x2.5mm-KEY
S2: SW; SW1
U1: CH32V305GBU6; QFN28_4X4
U2: 6219P33M; SOT-23
Y1: 8M; XT3225

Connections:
GND: C1.2, C4.2, C7.1, C8.1, C11.1, C12.2, C13.2, D1.2, P1.3, P1.4, P1.15, P1.17, P1.18, P1.19, P1.20, P2.1, P2.2, P2.17, P2.19, P2.20, P7.0, P7.A1, P7.B1, P8.0, P8.4, R22.2, R23.2, S1.2, U1.0, U1.20, U2.1, Y1.2, Y1.4
LED1: D4.2, P4.2
LED2: D3.2, P4.1
NetD1_1: D1.1, R1.1
NetD3_1: D3.1, R3.2
NetD4_1: D4.1, R6.2
NetF1_1: F1.1, S2.3
NetP7_A5: P7.A5, R22.1
NetP7_B5: P7.B5, R23.1
PA4/PA1: P1.16, U1.7
PA5: P2.18, U1.8
PA6: P2.15, U1.9
PA7: P2.16, U1.10
PA8: P2.5, U1.18
PA13: P2.6, U1.19
PA14: P2.8, U1.22
PB6: P1.9, P7.A7, P7.B7, P8.2, U1.27
PB7: P1.10, P7.A6, P7.B6, P8.3, U1.28
PB10: P2.13, U1.11
PB11: P2.14, U1.12
PB12: P2.11, U1.13
PB13: P2.12, U1.14
PB14: P2.9, U1.15
PB15: P2.10, U1.16
PC2: P1.14, U1.4
PC3: P1.13, U1.5
PC8: P2.7, U1.17
PC10: P1.5, U1.23
PC11: P1.6, U1.24
PC12: P1.7, U1.25
PD0: C7.2, P1.12, U1.1, Y1.3
PD1: C8.2, P1.11, U1.2, Y1.1
PD2: P1.8, U1.26
RST: C11.2, S1.1, U1.3
V5V: C12.1, F1.2, U2.3
VBUS: P1.1, P7.A4, P7.B4, P8.1, S2.1
VCC: C1.1, C13.1, P1.2, P2.3, P2.4, R1.2, R2.1, R3.1, R6.1, U1.21, U2.2
VIO: C4.1, R2.2, U1.6

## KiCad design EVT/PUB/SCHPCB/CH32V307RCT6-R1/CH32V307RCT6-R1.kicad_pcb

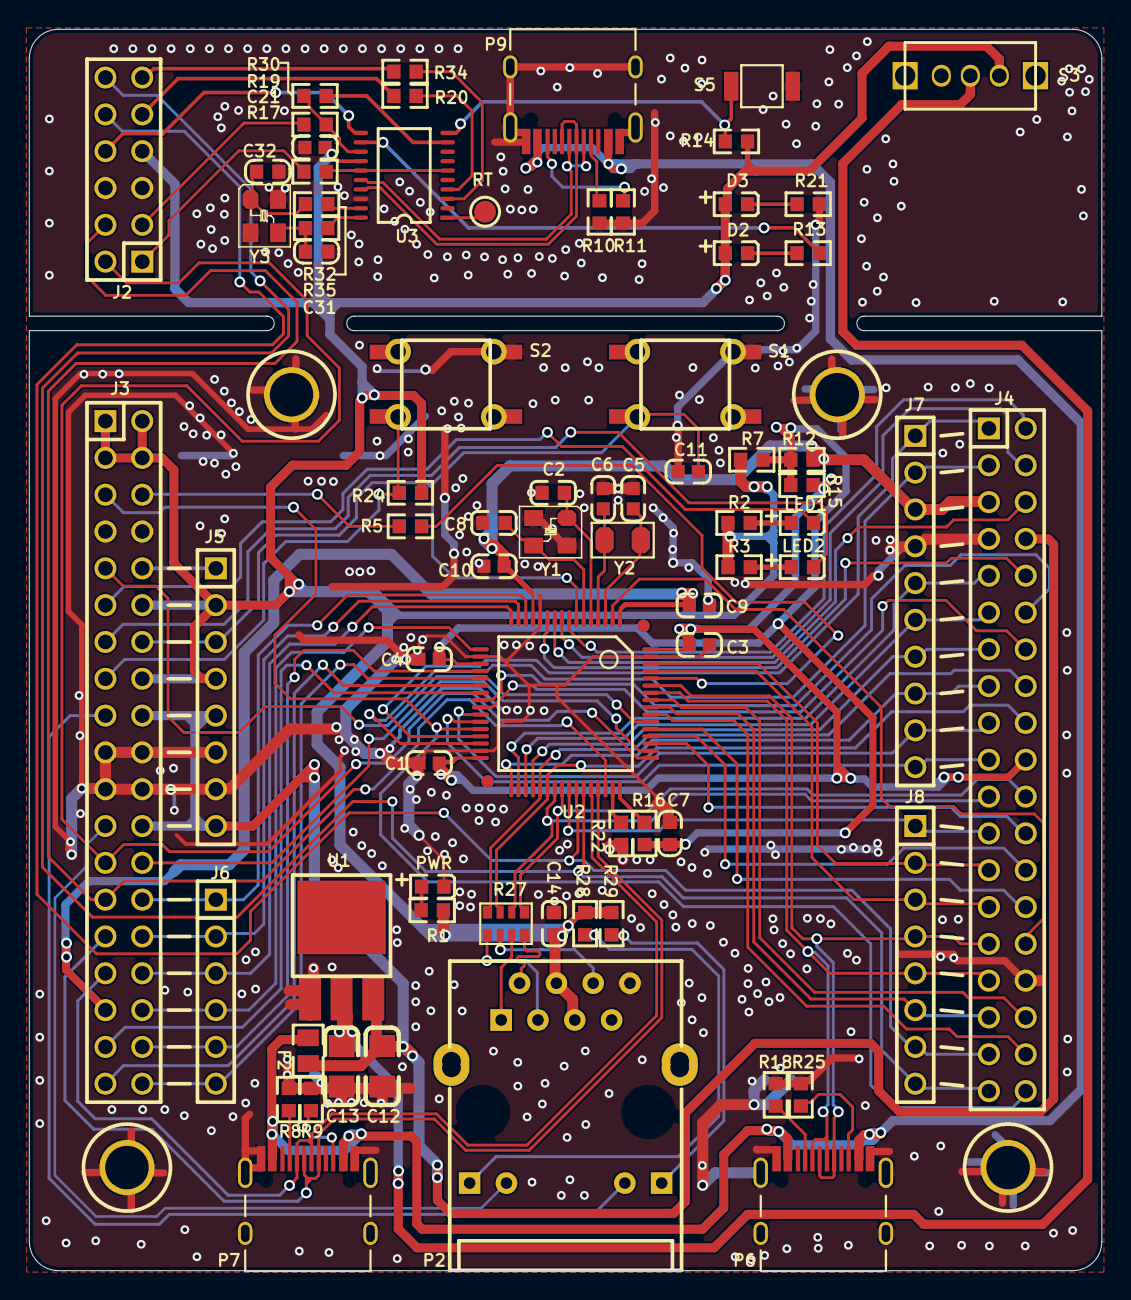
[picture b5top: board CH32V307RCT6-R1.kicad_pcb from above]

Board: 2 copper layers, 74.0 x 85.6 mm, 74 parts (0 on the bottom side), 107 nets.

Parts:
C1, C3, C4, C7, C9, C10, C11, C14, C21: 0.1uF; 0603_C
C2, C8: 22pF; 0603_C
C5, C6: 12pF; 0603_C
C12, C13: 10uF; 3216_C
C31, C32: NC(22pF); 0603_C
D2: BLUE; 0603+
D3: RED; 0603+
F2: 500mA; 0805
J2: Header 6X2; IDC12-2.54mm
J3, J4: Header 19X2; IDC38-2.54mm
J5, J8: Header 8; SIP8-2.54mm
J6: Header 6; SIP6-2.54MM
J7: Header 10; SIP10-2.54mm
LED1: LED1 blue; 0603+
LED2: LED2 blue; 0603+
P2: HR911105A
P6, P7, P9: TYPE-C; TYPE-C-Receptacle-2.0
PWR: POWER red; 0603+
R1, R2, R3, R13, R21, R28, R29, R30: 1K; 0603
R5, R14, R24: 10K; 0603
R7, R12, R15: 0Ω; 0603
R8, R9, R10, R11, R18, R25: NC(5.1K); 0603
R16, R22: 0; 0603
R17, R19: 100; 0603
R20, R34: 270; 0603
R27: 0Ω; 8P4R-0603
R32, R35: NC(0R); 0603
RT: Testpoint; TESTPOINT1
S1: RESET(Yellow); KEYX
S2: USER(Blue); KEYX
S3: SW; SW1
S5: KEY; 贴片按键
U1: 1117-3.3V; SOT-223
U2: CH32V307R; LQFP64M_10X10
U3: CH32V305F; TSSOP20
Y1: 8MHz; XT3225
Y2: 32.768k; FC-135
Y3: NC(12M); XT3225

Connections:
5V_in: F2.1, P6.A4, P6.B4, P7.A4, P7.B4, P9.A4, P9.B4
+5V: C12.1, F2.2, J3.18, J3.24, J4.8, J5.5, J5.8, U1.3
BOOT0: R5.2, U2.60
BOOT1: J3.5, J4.38, U2.28
CLK: J2.2, J3.25, U2.49
CLK0: J2.1, R17.1
DIO: J2.4, J3.27, U2.46
DIO0: J2.3, R19.1
D_SWCLK: R17.2, U3.6, U3.15
D_SWDIO: R19.2, R30.1, U3.13
ELED1: J3.23, P2.10
ELED2: J3.17, P2.11
ERXN: J4.18, R27.3, U2.38
ERXN1: P2.6, R27.6
ERXP: J4.16, R27.4, U2.37
ERXP1: P2.3, R27.5
ETXN: J4.22, R27.1, U2.40
ETXN1: P2.2, R27.8
ETXP: J4.21, R27.2, U2.39
ETXP1: P2.1, R27.7
GND: C1.1, C2.1, C3.1, C4.1, C5.2, C6.2, C7.1, C8.1, C9.2, C10.2, C11.1, C12.2, C13.2, C14.1, C21.2, C31.1, C32.1, J2.5, J2.6, J3.7, J3.8, J3.19, J3.20, J3.21, J3.22, J4.7, J4.32, J5.6, J5.7, J7.4, P2.8, P6.0, P6.A1, P6.B1, P7.0, P7.A1, P7.B1, P9.0, P9.A1, P9.B1, PWR.2, R8.1, R9.1, R10.2, R11.2, R18.1, R21.1, R22.1, R25.1, S1.3, S2.3, S5.2, U1.1, U2.12, U2.18, U2.31, U2.63, U3.18, Y1.2, Y1.4, Y3.2, Y3.4
IAP: R14.1, S5.1, U3.10
KEY: J3.15, R24.1, S2.1
LED1: J3.11, LED1.2
LED2: J3.13, LED2.2
LED_CON: R13.1, U3.12
NRST: C11.2, J3.14, J5.3, S1.1, U2.7
NetC13_1: C13.1, S3.1, U1.2
NetD2_2: D2.2, R13.2
NetD3_2: D3.2, R21.2
NetJ3_6: J3.6, R5.1
NetJ3_10: J3.10, J5.1
NetLED1_1: LED1.1, R2.2
NetLED2_1: LED2.1, R3.2
NetP2_9: P2.9, R28.2
NetP2_12: P2.12, R29.2
NetP6_A5: P6.A5, R18.2
NetP6_B5: P6.B5, R25.2
NetP7_A5: P7.A5, R8.2
NetP7_B5: P7.B5, R9.2
NetP9_A5: P9.A5, R10.1
NetP9_B5: P9.B5, R11.1
NetPWR_1: PWR.1, R1.1
NetR16_2: R16.2, U2.48
NetR22_2: R22.2, U2.47
OSC_IN: C32.2, R32.2, Y3.1
OSC_OUT: C31.2, R35.2, Y3.3
PA0: J3.28, J6.1, U2.14
PA1: J3.30, J6.2, U2.15
PA2: J3.32, J6.3, U2.16
PA3: J3.34, J6.4, U2.17
PA4: J3.36, J6.5, U2.20
PA5: J3.38, J6.6, U2.21
PA6: J3.37, U2.22
PA7: J3.35, U2.23
PA8: J4.23, J8.1, U2.41
PA9: J2.10, J4.35, J8.7, U2.42
PA10: J2.12, J4.37, J8.8, U2.43
PA11: J3.31, P7.A7, P7.B7, U2.44
PA12: J3.29, P7.A6, P7.B6, U2.45
PA15: J3.26, U2.50
PB0: J4.17, J7.9, U2.26
PB1: J4.19, J7.10, U2.27
PB3: J4.36, U2.55
PB4: J4.33, J8.6, U2.56
PB5: J4.34, U2.57
PB6: J4.31, J8.5, P6.A7, P6.B7, U2.58
PB7: J4.29, J8.4, P6.A6, P6.B6, U2.59
PB8: J4.27, J8.3, U2.61
PB9: J4.25, J8.2, U2.62
PB10: J4.1, J7.1, U2.29
PB11: J4.3, J7.2, U2.30
PB12: J4.15, J7.8, U2.33
PB13: J4.9, J7.5, U2.34
PB14: J4.11, J7.6, U2.35
PB15: J4.13, J7.7, U2.36
PC0: J4.2, U2.8
PC1: J4.4, U2.9
PC2: J4.6, U2.10
PC3: J4.10, U2.11
PC4: J4.12, U2.24
PC5: J4.14, U2.25
PC6_305: R30.2, U3.9
PC10: J4.24, U2.51
PC11: J4.26, U2.52
PC12: J4.28, U2.53
PC13: J4.30, U2.2
PC14: C5.1, U2.3, Y2.1
PC15: C6.1, U2.4, Y2.2
PD0: C2.2, U2.5, Y1.1
PD0_305: R32.1, U3.19
PD1: C8.2, U2.6, Y1.3
PD1_305: R35.1, U3.20
PD2: J3.9, U2.54
RST0: J2.8, U3.11
RT: RT.1, U3.1
RX_OUT: J2.9, R20.1
TX_OUT: J2.11, R34.1
UART3_RX: R20.2, U3.4
UART3_TX: R34.2, U3.3
USB_N: P9.A7, P9.B7, U3.16
USB_P: P9.A6, P9.B6, U3.17
VBAT: C9.1, J3.33, U2.1
VCC: C14.2, C21.1, D2.1, D3.1, J2.7, J3.1, J3.2, J3.3, J3.4, J3.12, J3.16, J5.2, J5.4, P2.4, P2.5, R1.2, R2.1, R3.1, R7.1, R14.2, R24.2, R28.1, R29.1, S3.3, U3.14
VDD: C4.2, C7.2, R7.2, R12.2, R15.2, R16.1, U2.19
VDDA: C10.1, J4.5, J7.3, R12.1, U2.13
VIO: C1.2, C3.2, J4.20, R15.1, U2.32, U2.64

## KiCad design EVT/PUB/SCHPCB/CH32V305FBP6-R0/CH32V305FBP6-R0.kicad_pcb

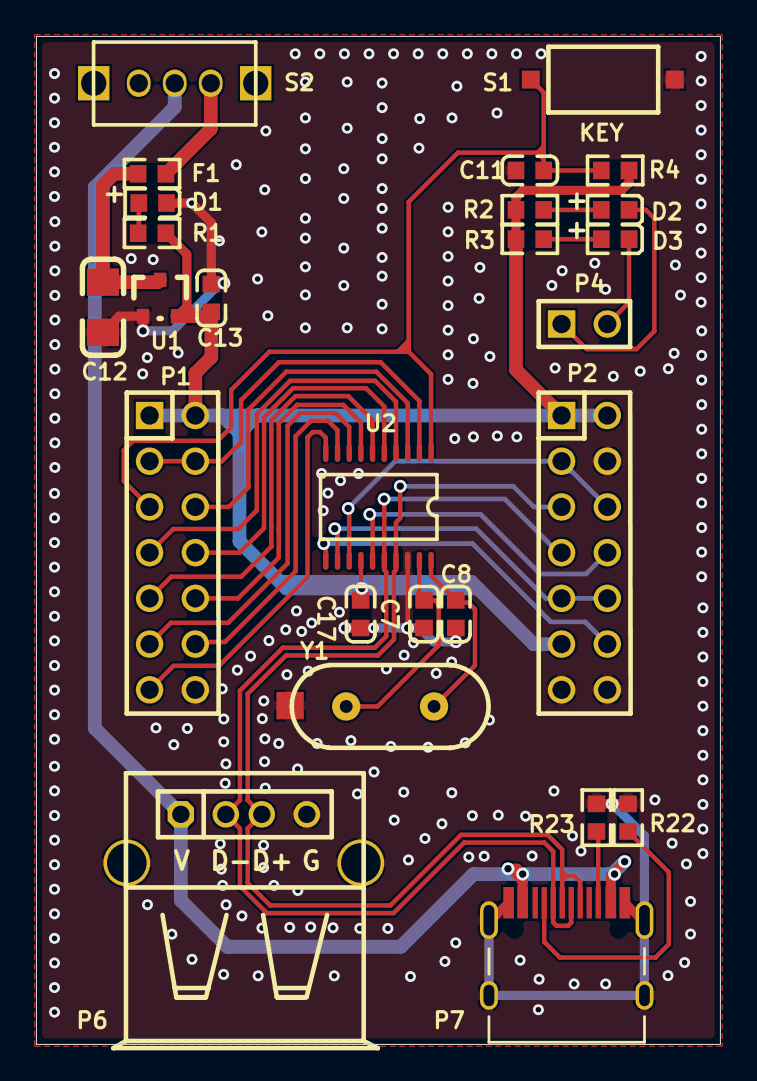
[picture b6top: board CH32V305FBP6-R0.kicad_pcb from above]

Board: 2 copper layers, 38.0 x 56.0 mm, 26 parts (0 on the bottom side), 30 nets.

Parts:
C7, C8: 22pF; 0603_C
C11, C17: 0.1uF; 0603_C
C12: 10uF; 3216_C
C13: 2.2uF; 0603_C
D1: POWER red; 0603+
D2: LED1; 0603+
D3: LED2; 0603+
F1: 500mA; 0603
P1, P2: HEADER 7x2; IDC14-2.54mm
P4: 2HEAD; SIP2-2.54mm
P6: USB_A; USBAF
P7: TYPE-C; TYPE-C-Receptacle-2.0
R1, R2, R3: 1K; 0603
R4: 10K; 0603
R22, R23: NC(5.1K); 0603
S1: KEY; SMD_6.1x3.65x2.5mm-KEY
S2: SW; KEY2
U1: 6219; SOT-23
U2: CH32V305F; TSSOP20
Y1: 8M; XT_AT49

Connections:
+5V: P6.1, P7.A4, P7.B4, S2.1
GND: C7.1, C8.1, C11.1, C12.2, C13.1, C17.1, D1.2, P1.14, P2.4, P2.13, P2.14, P6.0, P6.4, P7.0, P7.A1, P7.B1, R22.2, R23.2, S1.2, U1.1, U2.18, Y1.0
LED1: D2.2, P4.1
LED2: D3.2, P4.2
NRST: C11.2, P1.5, R4.1, S1.1, U2.1
NetD1_1: D1.1, R1.1
NetD2_1: D2.1, R2.2
NetD3_1: D3.1, R3.2
NetF1_1: F1.1, S2.3
NetP7_A5: P7.A5, R22.1
NetP7_B5: P7.B5, R23.1
PA1: P1.3, P1.4, U2.2
PA8: P2.9, P2.10, U2.12
PA9: P2.3, P2.6, U2.13
PA14: P2.8, U2.15
PB6: P2.7, P6.2, P7.A7, P7.B7, U2.16
PB7: P2.5, P6.3, P7.A6, P7.B6, U2.17
PB10: P1.6, U2.3
PB11: P1.7, U2.4
PB12: P1.8, U2.5
PB13: P1.9, U2.6
PB14: P1.10, U2.7
PB15: P1.11, U2.8
PC6: P1.12, U2.9
PC7: P1.13, U2.10
PC8: P2.12, U2.11
PD0: C7.2, U2.19, Y1.2
PD1: C8.2, U2.20, Y1.1
V5V: C12.1, F1.2, U1.3
VCC: C13.2, C17.2, P1.1, P1.2, P2.1, P2.2, P2.11, R1.2, R2.1, R3.1, R4.2, U1.2, U2.14
